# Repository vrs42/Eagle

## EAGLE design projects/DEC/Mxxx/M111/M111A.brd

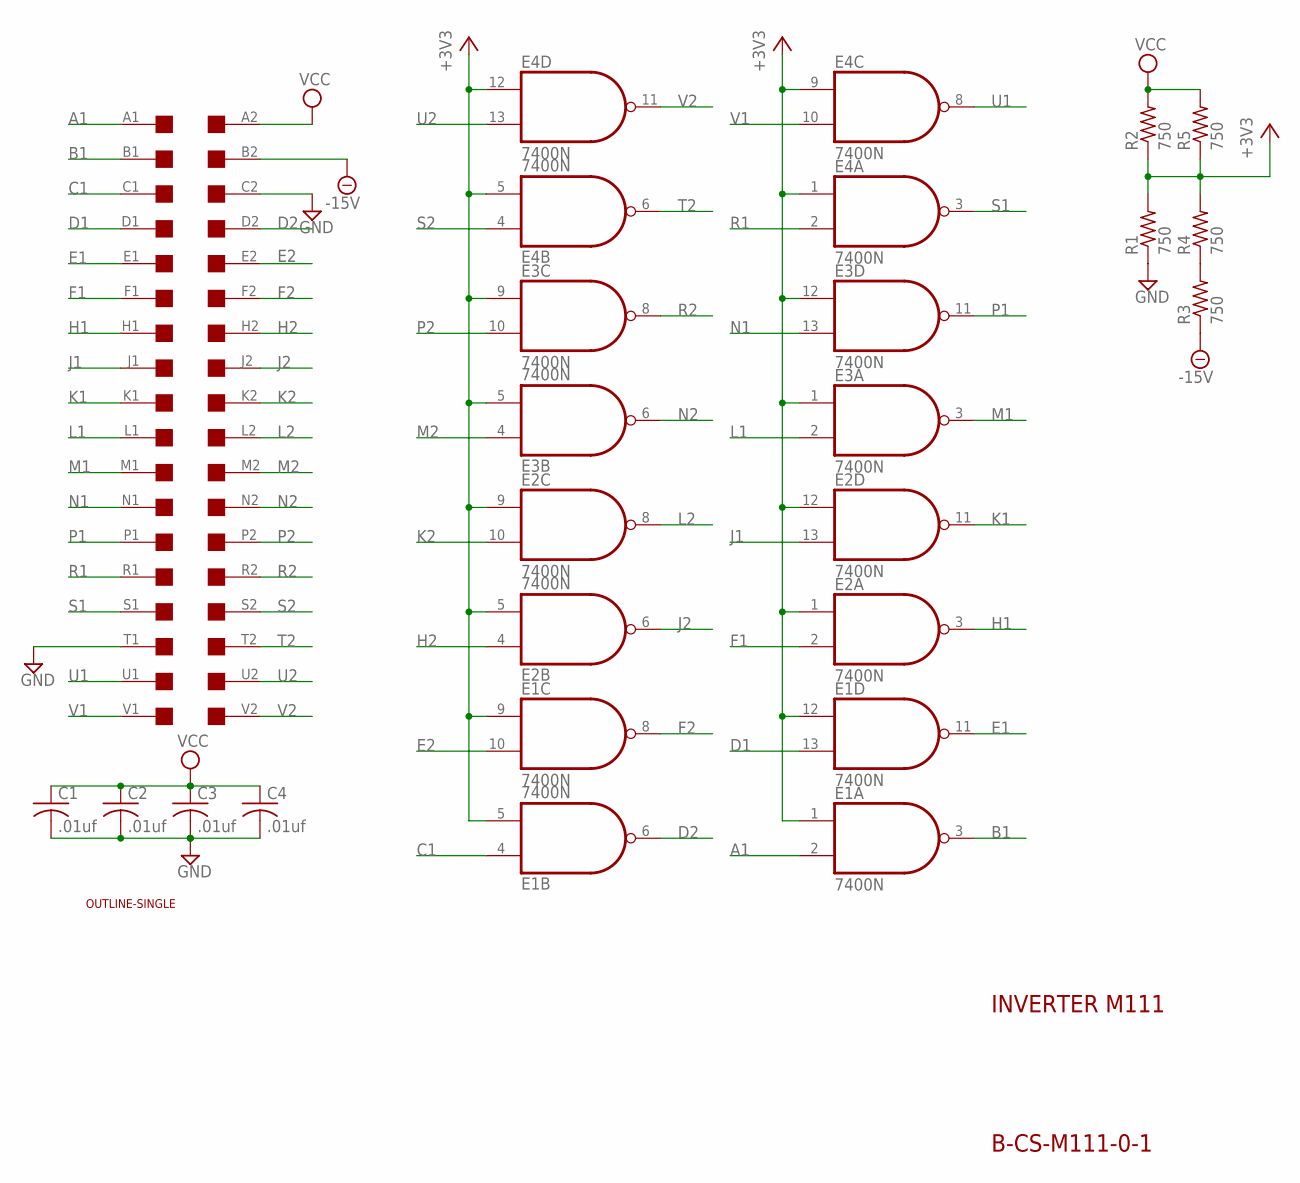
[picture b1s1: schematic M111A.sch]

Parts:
A: EDGE-2CONNECTOR; EDGE-CON2
C1, C2, C3, C4: .01uf; C050-025X075
E1, E2, E3, E4: 7400N; DIL14
R1, R2, R3, R4, R5: 750; 0207/10
U$1: OUTLINE-SINGLE; SINGLE

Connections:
+3V3: E1.1 (I0), E1.5 (I1), E1.9 (I0), E1.12 (I0), E2.1 (I0), E2.5 (I1), E2.9 (I0), E2.12 (I0), E3.1 (I0), E3.5 (I1), E3.9 (I0), E3.12 (I0), E4.1 (I0), E4.5 (I1), E4.9 (I0), E4.12 (I0), R1.2, R2.1, R4.2, R5.1
-15V: A.B2, R3.1
A1: A.A1, E1.2 (I1)
B1: A.B1, E1.3 (O)
C1: A.C1, E1.4 (I0)
D1: A.D1, E1.13 (I1)
D2: A.D2, E1.6 (O)
E1: A.E1, E1.11 (O)
E2: A.E2, E1.10 (I1)
F1: A.F1, E2.2 (I1)
F2: A.F2, E1.8 (O)
GND: A.C2, A.T1, C1.2, C2.2, C3.2, C4.2, E1.7 (GND), E2.7 (GND), E3.7 (GND), E4.7 (GND), R1.1
H1: A.H1, E2.3 (O)
H2: A.H2, E2.4 (I0)
J1: A.J1, E2.13 (I1)
J2: A.J2, E2.6 (O)
K1: A.K1, E2.11 (O)
K2: A.K2, E2.10 (I1)
L1: A.L1, E3.2 (I1)
L2: A.L2, E2.8 (O)
M1: A.M1, E3.3 (O)
M2: A.M2, E3.4 (I0)
N1: A.N1, E3.13 (I1)
N2: A.N2, E3.6 (O)
unnamed: R3.2, R4.1
P1: A.P1, E3.11 (O)
P2: A.P2, E3.10 (I1)
R1: A.R1, E4.2 (I1)
R2: A.R2, E3.8 (O)
S1: A.S1, E4.3 (O)
S2: A.S2, E4.4 (I0)
T2: A.T2, E4.6 (O)
U1: A.U1, E4.8 (O)
U2: A.U2, E4.13 (I1)
V1: A.V1, E4.10 (I1)
V2: A.V2, E4.11 (O)
VCC: A.A2, C1.1, C2.1, C3.1, C4.1, E1.14 (VCC), E2.14 (VCC), E3.14 (VCC), E4.14 (VCC), R2.2, R5.2

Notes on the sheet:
INVERTER M111
B-CS-M111-0-1

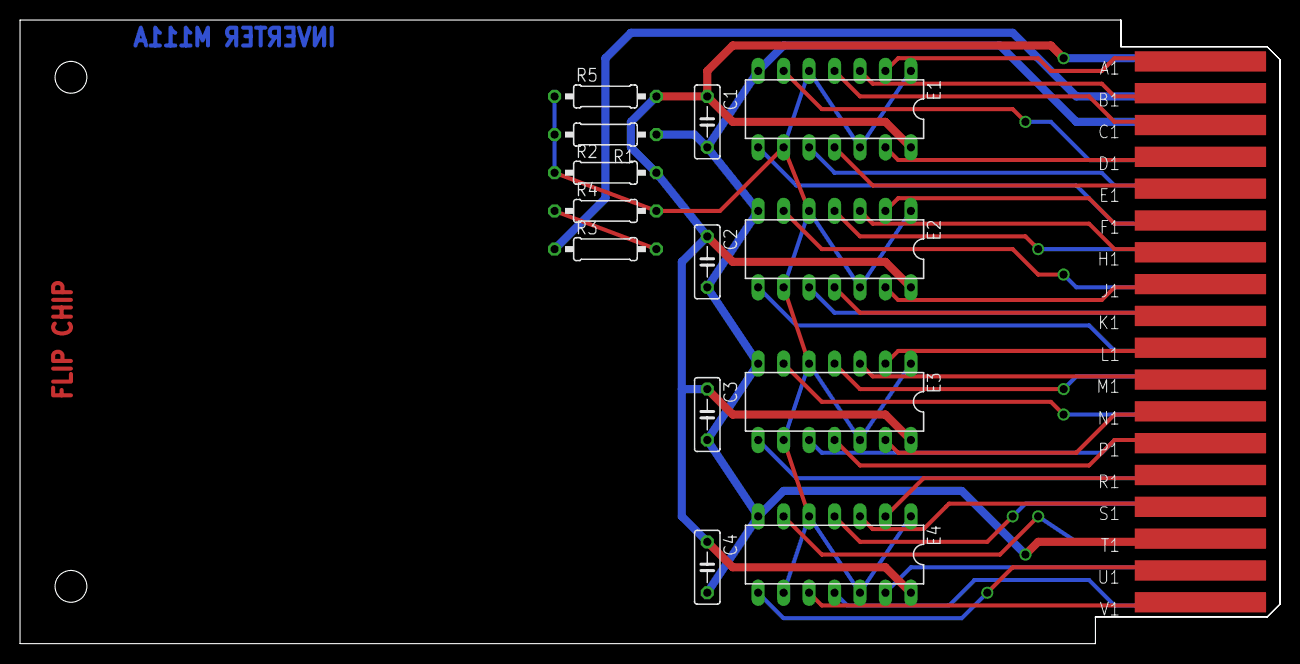
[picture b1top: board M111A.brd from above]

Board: 2 copper layers, 125.7 x 62.2 mm, 15 parts (0 on the bottom side), 37 nets.

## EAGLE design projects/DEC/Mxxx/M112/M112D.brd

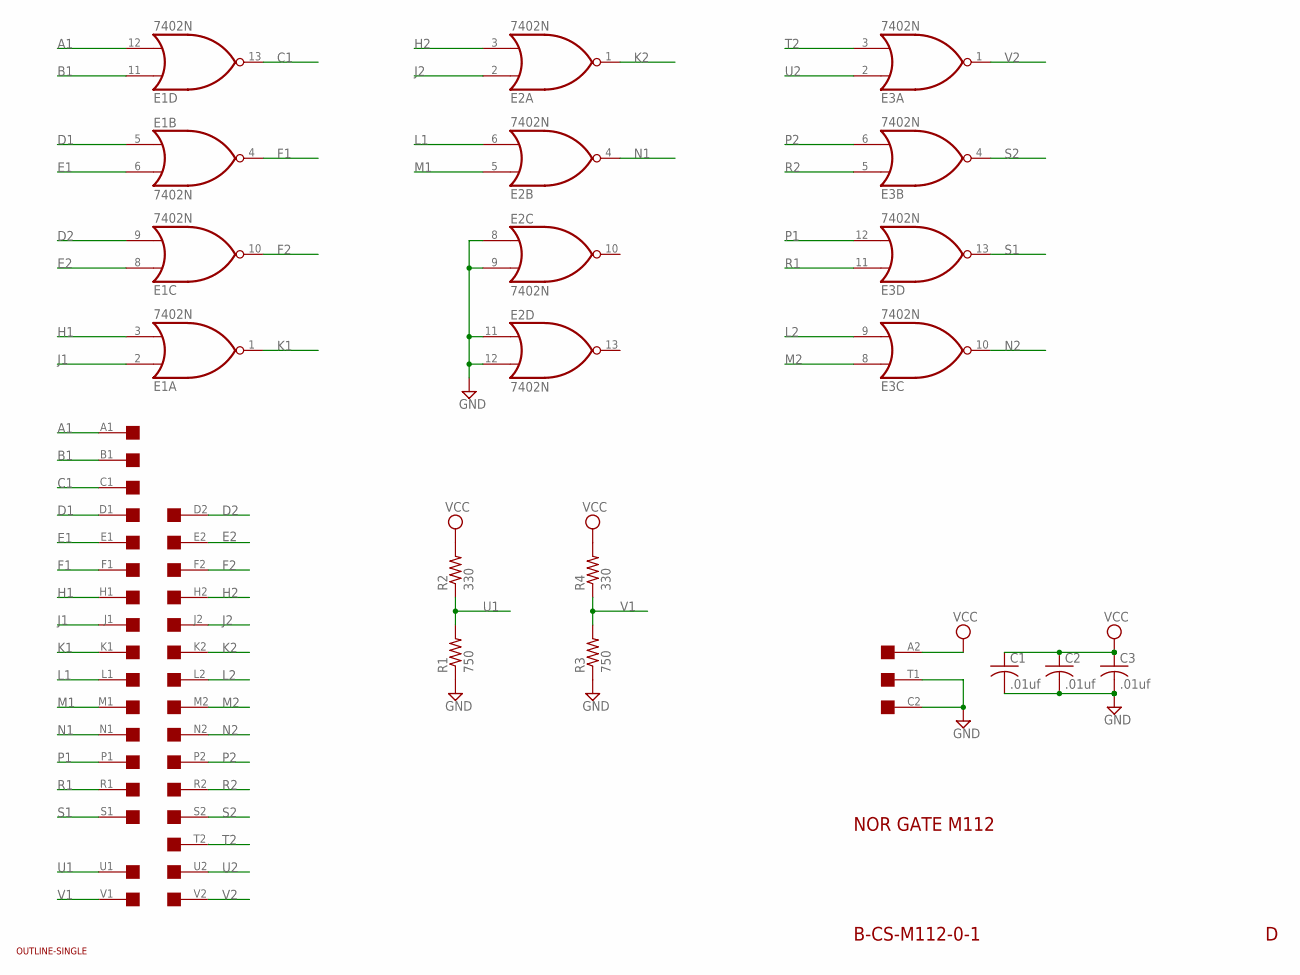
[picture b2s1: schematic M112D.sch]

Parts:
C1, C2, C3: .01uf; C050-025X075
E1, E2, E3: 7402N; DIL14
R1, R3: 750; 0207/10
R2, R4: 330; 0207/10
U$1: SINGLE; EDGE-CON2
U$4: OUTLINE-SINGLE; SINGLE

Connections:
A1: E1.12 (I1), U$1.A1
B1: E1.11 (I0), U$1.B1
C1: E1.13 (O), U$1.C1
D1: E1.5 (I0), U$1.D1
D2: E1.9 (I1), U$1.D2
E1: E1.6 (I1), U$1.E1
E2: E1.8 (I0), U$1.E2
F1: E1.4 (O), U$1.F1
F2: E1.10 (O), U$1.F2
GND: C1.2, C2.2, C3.2, E1.7 (GND), E2.7 (GND), E2.8 (I0), E2.9 (I1), E2.11 (I0), E2.12 (I1), E3.7 (GND), R1.1, R3.1, U$1.C2, U$1.T1
H1: E1.3 (I1), U$1.H1
H2: E2.3 (I1), U$1.H2
J1: E1.2 (I0), U$1.J1
J2: E2.2 (I0), U$1.J2
K1: E1.1 (O), U$1.K1
K2: E2.1 (O), U$1.K2
L1: E2.6 (I1), U$1.L1
L2: E3.9 (I1), U$1.L2
M1: E2.5 (I0), U$1.M1
M2: E3.8 (I0), U$1.M2
N1: E2.4 (O), U$1.N1
N2: E3.10 (O), U$1.N2
P1: E3.12 (I1), U$1.P1
P2: E3.6 (I1), U$1.P2
R1: E3.11 (I0), U$1.R1
R2: E3.5 (I0), U$1.R2
S1: E3.13 (O), U$1.S1
S2: E3.4 (O), U$1.S2
T2: E3.3 (I1), U$1.T2
U1: R1.2, R2.1, U$1.U1
U2: E3.2 (I0), U$1.U2
V1: R3.2, R4.1, U$1.V1
V2: E3.1 (O), U$1.V2
VCC: C1.1, C2.1, C3.1, E1.14 (VCC), E2.14 (VCC), E3.14 (VCC), R2.2, R4.2, U$1.A2

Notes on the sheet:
NOR GATE M112
B-CS-M112-0-1

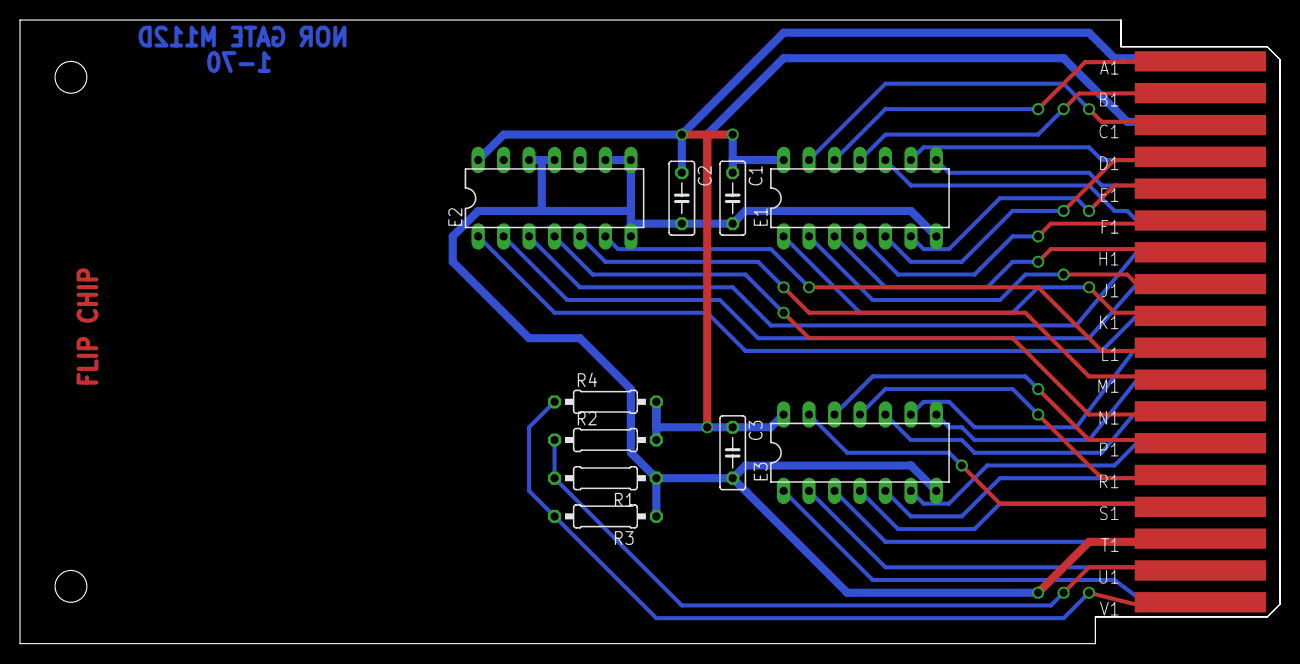
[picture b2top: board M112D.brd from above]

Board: 2 copper layers, 125.7 x 62.2 mm, 12 parts (0 on the bottom side), 34 nets.
